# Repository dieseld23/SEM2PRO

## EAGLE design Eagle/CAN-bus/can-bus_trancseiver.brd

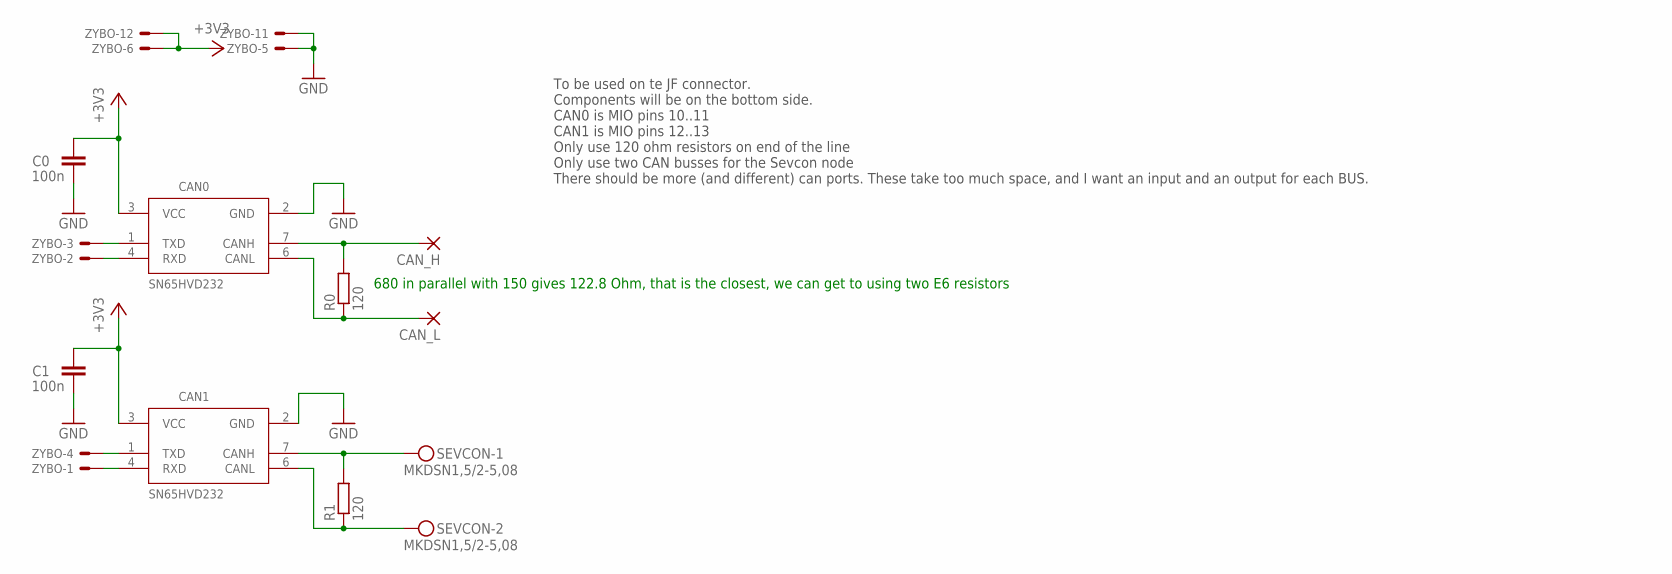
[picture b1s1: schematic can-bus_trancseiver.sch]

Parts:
C0, C1: 100n; C0805K
CAN0, CAN1: SN65HVD232; SO08
CAN_H: 1,6/0,8
CAN_L: 1,6/0,8
R0, R1: 120; R0805
SEVCON: MKDSN1,5/2-5,08
ZYBO: PMOD12

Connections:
+3V3: C0.1, C1.1, CAN0.3 (VCC), CAN1.3 (VCC), ZYBO.6, ZYBO.12
GND: C0.2, C1.2, CAN0.2 (GND), CAN1.2 (GND), ZYBO.5, ZYBO.11
unnamed: CAN0.1 (TXD), ZYBO.3
unnamed: CAN0.4 (RXD), ZYBO.2
unnamed: CAN1.1 (TXD), ZYBO.4
unnamed: CAN1.4 (RXD), ZYBO.1
unnamed: CAN0.7 (CANH), CAN_H.1, R0.2
unnamed: CAN1.7 (CANH), R1.2, SEVCON.1
unnamed: CAN1.6 (CANL), R1.1, SEVCON.2
unnamed: CAN0.6 (CANL), CAN_L.1, R0.1

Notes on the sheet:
To be used on te JF connector. Components will be on the bottom side. CAN0 is MIO pins 10..11 CAN1 is MIO pins 12..13 Only use 120 ohm resistors on end of the line Only use two CAN busses for the Sevcon node There should be more (and different) can ports. These take too much space, and I want an in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
680 in parallel with 150 gives 122.8 Ohm, that is the closest, we can get to using two E6 resistors

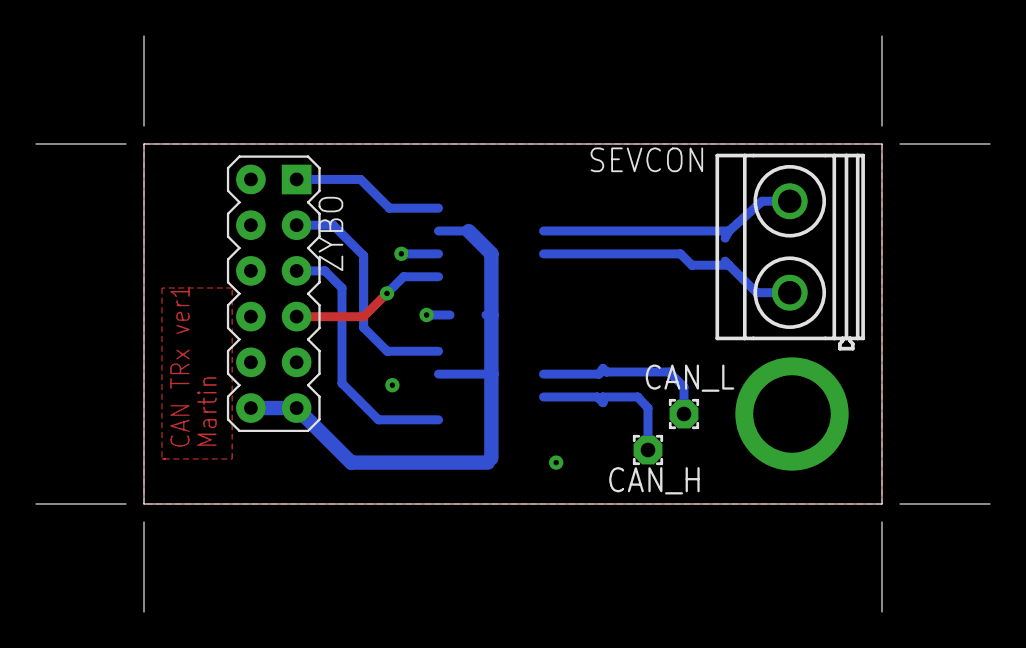
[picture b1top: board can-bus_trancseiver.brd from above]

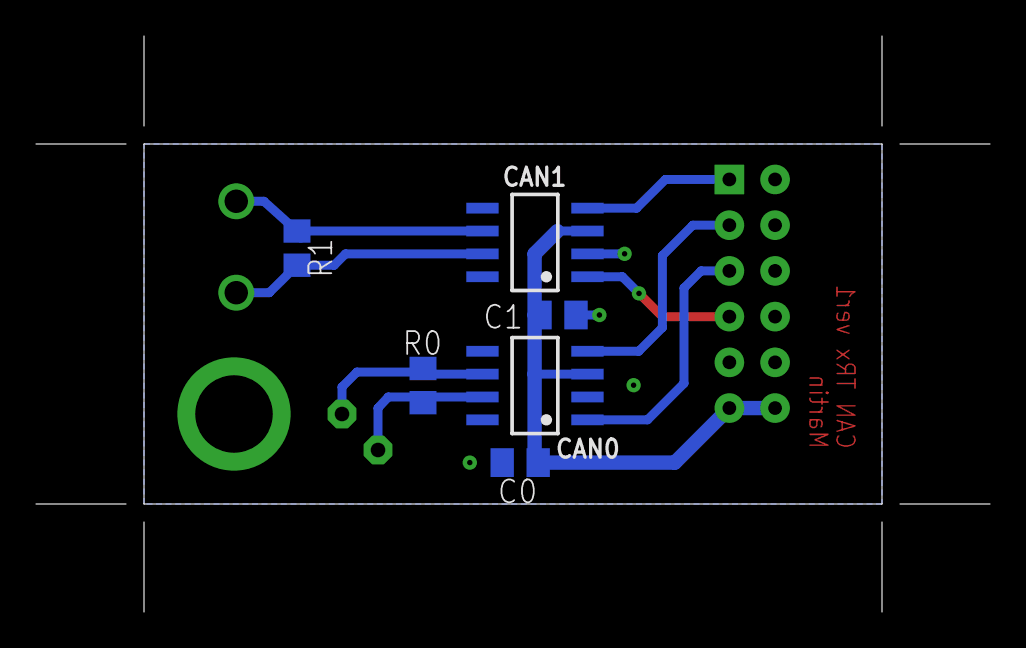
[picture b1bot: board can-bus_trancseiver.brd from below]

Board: 2 copper layers, 53.0 x 32.0 mm, 10 parts (6 on the bottom side), 10 nets.

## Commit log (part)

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2016-10-04 Added a report structure
2016-10-04 Oops. We need gitignore file. But it is too late for me now....
2016-10-05 Added some questions to think about in systemdescription.tex
2016-10-05 Added questions and gitignore
2016-10-06 Added some answers.STILL NOT FINISHED!
2016-10-06 changes to .gitignore
2016-10-06 Added some questions
2016-10-06 Questions as list items, plus some questions
2016-10-06 committing in order to pull
2016-10-06 First try at system descriptuion
2016-10-06 Added a bit about further investigation
2016-10-07 added detail about data consumers
2016-10-07 Pulling
2016-10-07 Keep committing
2016-10-07 Changes according to our discussion
2016-10-07 removed two-side report
2016-10-07 One days work
2016-10-08 Logging rate
2016-10-09 Noting of importance
2016-10-09 Added section on parameters to monitor
2016-10-09 added *.dvi to gitignore
2016-10-09 Adding the topology analysis
2016-10-09 added my section about wireless
2016-10-09 Network technology section, a small one
2016-10-09 Network technology section added.
2016-10-09 just a few notes
2016-10-10 Notes on localnetwork_requirements.tex
2016-10-10 Commiting AND pushing
2016-10-10 typos
2016-10-10 Added datasheet to Sevcon
2016-10-10 typos and added conclusion and scope to parameter discussion
2016-10-10 added eps-converted-to.pdf to .gitignore
2016-10-10 Prettier picture
2016-10-10 Committing some new changes about my part
2016-10-10 Found the CAN tranceiver, added to localnetwork_requirements.tex
2016-10-10 disabled todos
2016-10-10 Added a very tough question for Catalin. Also added him as author, and changed it to 2nd semester.
2016-10-12 CANopen and CANopenSocket for Linux + Bus topology
2016-10-12 added links
2016-10-12 Small changes
2016-10-12 Added requirements to my section + more. Changed the introduction to reflect that we don't want to change parameters
2016-10-13 Pulling basically
2016-10-13 Fixed an error due to a character.
2016-10-13 added use case diagram
2016-10-13 I want to pullcd M.E.Electronics/Project_2/SEM2PRO/! So, committing.
2016-10-14 Worked a little on interfacing_with_zevcon. Contacted KHA about additional documentation, not readily available online
2016-10-14 Added a lot of documentation about the sevcon, that I got from Karsten
2016-10-23 interfacing_with_sevcon
2016-10-25 timetable finally heregit add time_table.xlsx git add time_table.xlsx
2016-10-28 added system requirements - or at least I tried :)
2016-10-28 PCB layouts
2016-10-31 Second attempt to create a PCB
2016-11-01 system requirements changed after meeting
2016-11-06 Commit after reinstall
2016-11-07 added gps data
2016-11-10 unknown changes to systemdescription
2016-11-10 templates for creating c and h files.
2016-11-10 added gps code
2016-11-13 Tried getting a better structure and tried making a system description
2016-11-13 Committing?
2016-11-13 Adding part of Testing of CAN stack
2016-11-13 Committing Testing the stack board
2016-11-14 The missing picture!
2016-11-14 Vivado test project
2016-11-14 Added new go_kart_network_simple.png
2016-11-14 Added a usecase. Fixed todo problem
2016-11-14 Now without borders!
2016-11-15 added graphics and wifi section
2016-11-16 Intermediary commit and push. Wrote something about CAN protocol, and added pictures.
2016-11-16 pre pull commit
2016-11-16 added canbus image
2016-11-16 added introduction to system analysis and an analysis on micro-controller
2016-11-16 Written a lot about the CAN bus
2016-11-16 Final stuff written about the Can_protocol.tex for now.
2016-11-17 something...
2016-11-21 updates to canbus_setup
2016-11-21 Added analysis_nodes image
2016-11-21 Added todos/corrections to the CAN bus section
2016-11-21 added eps version of canbus_setup
2016-11-21 Uploaded analysis_nodes in eps format
2016-11-21 slight changes to CAN section
2016-11-21 pre-pull commit
2016-11-21 pre-going home commit
2016-11-21 added something about software on stationary computer
2016-11-21 Added new PC part to analysis_complex
2016-11-21 Added stand alone pc software image and eps of complex
2016-11-21 actually added images now..
2016-11-22 small changes..
2016-11-22 Uploaded PDF of Can xcvr schematic Wrote something about IMU
2016-11-22 I want to pull!
2016-11-23 REarranged the report a little bit, and wrote some comments about wifi.tex. Also extended the part about IMU
2016-11-23 I don't remember my changes
2016-11-24 Adding a new file - CAN_Implementation.tex
2016-11-24 Adding a png
2016-11-24 added appendixes
2016-11-25 pre pull
2016-11-25 wrote a bit about can bus testing
2016-11-29 added code for wifi
2016-11-29 added netsetup.sh script for joining ad-hoc network
2016-11-29 pre pull
    Also got results from the first of the four Bus tests.
2016-11-29 added figure for test setup of CAN
2016-11-29 Can network v2 Project files
2016-11-30 Restructured the report, added netsetup script
2016-11-30 added correct netsetup.sh ... derp...
2016-11-30 Can network v3 Vivado Project
2016-12-02 some last minute changes
2016-12-02 added lots of things
2016-12-02 Got test measurements for the BUS test
2016-12-02 Color changed
2016-12-05 Wrote more about can bus tests, and added some screen shots of the whiteboard
2016-12-05 Protocol functions implemented
2016-12-05 Protocol functions implemented + printf
2016-12-05 Added the protocol test program using bitwise operations
2016-12-05 Added two seq diagrams files
2016-12-05 AMP part first version
2016-12-06 changed my code
2016-12-07 more code
2016-12-07 README file for Vivado complete
2016-12-07 Update README.txt
    Github messed my tabs! WHY!?
2016-12-07 SeqDiagrams and a little bit of text improvements
2016-12-07 pre-pull
2016-12-07 Aded Object Dictionary.xlsx. Feel free to peruse and comment
2016-12-07 added acronyms and ui_backend
2016-12-08 Added stuff to .gitignore, added v2 of backend - supposedly the final version
2016-12-08 Trying to pull
2016-12-08 more code....
2016-12-08 Thomas Backend Class Diagr
2016-12-09 'final-draft' of Wifi/backend docs
2016-12-09 finished OD, wrote some about power requirements
2016-12-12 added files and documented code in .cpp and .hpp files
2016-12-12 First draft of introduction + moved use case narratives to appendix
2016-12-12 a little bit of writing
2016-12-12 Added new use case diagram, deleted the old, colorful and ugly one
2016-12-12 added some node software text and requirements
2016-12-13 Finished part on GPS analysis
2016-12-13 Recommit
2016-12-13 Refactoring mark 2
2016-12-13 My changes to pull Mark 2
2016-12-13 Some of CAN changes to resolve merge conflicts
2016-12-13 Started writing the CAN_functions.tex
2016-12-13 Some text moves and changes
2016-12-14 Added a CAN_Software.tex file
2016-12-14 removed space
2016-12-14 Added a file, some text added about the code
2016-12-14 Finished CAN_functions.tex
2016-12-14 changed subsections to sections etc. in verification part
2016-12-14 Proofing CAN_Implementation.tex
2016-12-14 added a missing file. It is now not missing :D
2016-12-14 State Diagram for Mikkel Node
2016-12-14 NOW IT'S PERFECT
2016-12-14 changes to protocol
2016-12-14 This is a good commit message
2016-12-14 Flow charts for Mikkel
2016-12-14 made a comment
2016-12-14 Re-cropped Flow charts for Mikkel
2016-12-14 variable text changes
2016-12-14 Re-Re-cropped Flow charts for Mikkel
2016-12-14 New section on protocol
2016-12-14 pumpernickel
2016-12-14 Made a few grammatical changes to wifi.tex. Otherwise very readable for the group's resident Linux noob.
2016-12-14 made a mistake. Fixed mistake
2016-12-15 something!
2016-12-15 Va hilvede ReX3-Cropped Flowcharts 4 Mikkel
2016-12-15 nice figures
2016-12-15 60th commitgit add FlowChart_CANSoft_*! with new FlowCharts
2016-12-15 corrections
2016-12-15 read through some of the early analysis
2016-12-15 Added power reqs to embedded platform analysis, finished first runthrough of analysis
2016-12-15 Mikkel Class Diagram Node Simple
2016-12-15 Catalin made me do this!
2016-12-15 Mikkel diagram StateDiagram_ConcatMsgProcess.pdf
2016-12-15 data for Thomas
2016-12-15 added section on wifi verification
2016-12-15 Mikkel StateDiagram_CANFrameProcess.pdf
2016-12-15 Mikkel Diagrams
2016-12-15 Wrote about data logging
2016-12-15 made code more clever and according to OD
2016-12-15 oh well look at the time.
2016-12-16 Non-toilet push
2016-12-16 Satisfying Martin's concern
2016-12-16 Fixed some todos
2016-12-16 maybe introduces an error with last commit - but it is fixed now
2016-12-16 Finished most todos and text polished a little bit
2016-12-16 Colors added for Mikkel
2016-12-16 Mikkel ClassDiagram_NodeWiFi.pdf
2016-12-16 Added first draft of frontend verification
2016-12-16 added
2016-12-16 Moved OD, cut away some of the analysis
2016-12-16 added wifi_node graphic
2016-12-16 removed png version of wifi_node
2016-12-16 Moved some text around and stuff and such and all.
2016-12-16 Mikkel Update diagrams
2016-12-16 Added at pretty picture and conformed colors on another one.
2016-12-16 NO MORE COLORS for Mikkelgit pushgit pushgit pushgit push!
2016-12-16 last draft of frontend verification, added associated graphic
2016-12-16 I think the Nodes section is finished
2016-12-16 Correct diagrams
2016-12-16 added appendix on adding nodes
2016-12-16 Wrote future_work.tex
2016-12-16 Added Use Case Narratives for the developer
2016-12-16 End of day commit.
2016-12-16 GPS sensor implementation finished?
2016-12-16 some IMU text
2016-12-16 verification node software finished
2016-12-16 added text to appendix and removed some of my todos
2016-12-17 changed font in listings
2016-12-17 nothing
2016-12-17 more text in appendix
2016-12-17 just some small changes
2016-12-17 Quick run through of implementation_of_node_software.tex
2016-12-17 OD table fixed
2016-12-17 Done going through sensor nodes
2016-12-17 Nuked todo
2016-12-17 ready for final readthrough
2016-12-17 Got to page 20
2016-12-18 So many changes!
2016-12-18 Finished first read through
2016-12-18 changed frontend figure
2016-12-18 Commented include appendixes in main file
2016-12-18 fixed figure and text
2016-12-18 Update figures
2016-12-18 Got the OD table fitted in nicely
2016-12-18 AXI CAN IP moved to Analysis and rewritten
2016-12-18 Rewrite of introduction
2016-12-18 added a todo
2016-12-18 Analysis conclusion finished.
2016-12-18 Wrote abstract+thanks
2016-12-18 names in todos now, changed CANPS part in implementation and basic communication in verification part
2016-12-18 Fixed hyperref. No one knows what the fudge wrong
2016-12-18 Rewritten Implementing CAN Utilizing XCanPs
2016-12-18 fixed my citation
2016-12-18 read and corrected 12 conclusion
2016-12-18 init conclusion
2016-12-18 Accessing CAN Controller from Linux section is now beautifull :D
2016-12-18 Future Work - AMP
2016-12-18 split lines in the bib.tex
2016-12-18 finished CAN ON ZYBO subsubsection
2016-12-18 tried to beautify the table of requirement. Added another beautifull thing in case that you don't like the table itself. Be sure to give me feedback :D :P :)
2016-12-18 sd-cards....
2016-12-18 Todo or not todo!
2016-12-18 not finished version of the conclusion
2016-12-18 Fixed some todo's
2016-12-18 first draft of conclusion
2016-12-18 added brandnew section about timestamping
2016-12-18 Done almost all Todo.txt
2016-12-18 future work added - not finished
2016-12-18 made some text more understandable
2016-12-18 Unidiotified the code
2016-12-18 added brand new subsection to future work
2016-12-18 JESUS IS NOT ALIVE!
2016-12-18 God damn quotes FIXEDgit pullgit pull
2016-12-18 "The Might and Vigor of Trump" - Thomas
2016-12-18 fixed GoCAN protocol section
2016-12-18 Changed TOC captions of figures and tables
2016-12-18 Fixed last FIFO
2016-12-18 use case narratives changed
2016-12-18 the woman is gone
2016-12-18 new introduction to verification
2016-12-18 little
2016-12-18 removed lines
2016-12-18 Fixed minor details
2016-12-18 did new implementation section
2016-12-18 small thing in abstract
2016-12-18 pre puuuuuuuuuuuuuuull
2016-12-18 read and accepted mikkels new real time stuff
2016-12-18 made few alterations to the can validation part
2016-12-18 comments
2016-12-18 changed backend to frontend in code
